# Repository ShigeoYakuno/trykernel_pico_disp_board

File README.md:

# trykernel_pico_disp_board

### 液晶のON/OFF回路
- MOSFETを使います
- 秋月で売っている30円のBSS138 Panjit製を使います
- Vthが1.5Vと使いやすいです
- 300mAしか引けませんが、液晶は100mA程度なので問題ないでしょう
- NチャネルのMOSFETです
- 

### MOSFETの基本回路通りに構成

- 基本回路どおりに設計します
- マイコン側に電流が流れる可能性があるので、直接受けず、抵抗を介します
- オープンドレイン接続を想定し、ゲートはプルダウンしておきます

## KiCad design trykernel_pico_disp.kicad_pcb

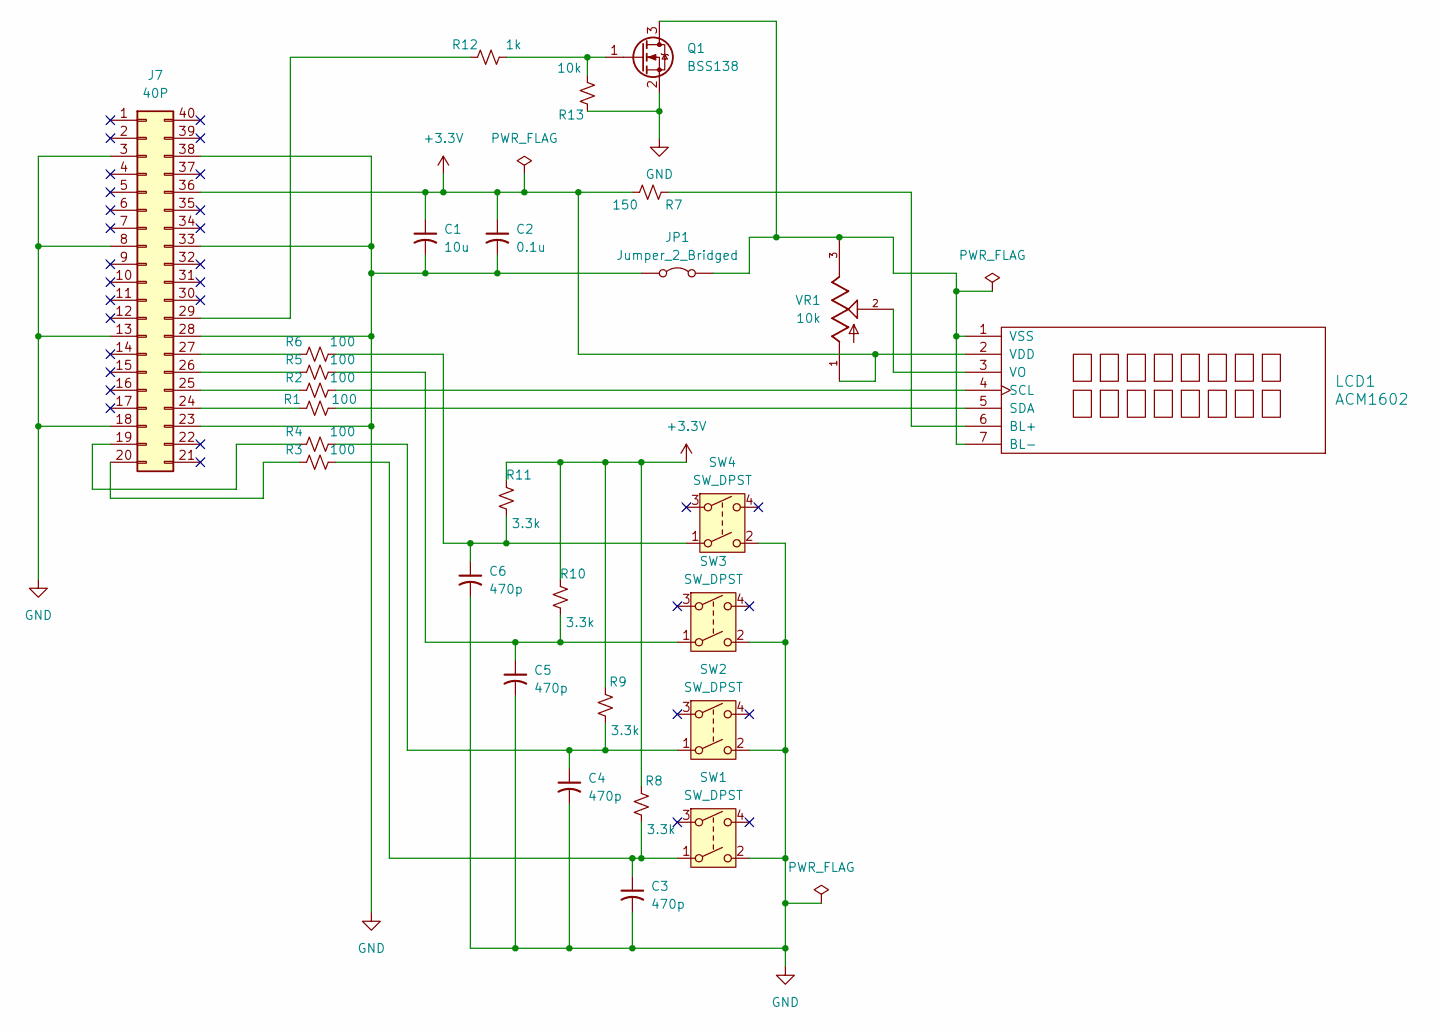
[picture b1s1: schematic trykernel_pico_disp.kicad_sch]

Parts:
C1: 10u; C_0603_1608Metric_Pad1.08x0.95mm_HandSolder
C2: 0.1u; C_0603_1608Metric_Pad1.08x0.95mm_HandSolder
C3, C4, C5, C6: 470p; C_0603_1608Metric_Pad1.08x0.95mm_HandSolder
J7: 40P; RPI_Hat_B+
JP1: Jumper_2_Bridged; PinHeader_1x02_P2.54mm_Vertical
LCD1: ACM1602; I2C_LCD-ACM1602NI-FLW-FBW-M01
Q1: BSS138; SOT-23
R1, R2, R3, R4, R5, R6: 100; R_0603_1608Metric_Pad0.98x0.95mm_HandSolder
R7: 150; R_0603_1608Metric_Pad0.98x0.95mm_HandSolder
R8, R9, R10, R11: 3.3k; R_0603_1608Metric_Pad0.98x0.95mm_HandSolder
R12: 1k; R_0603_1608Metric_Pad0.98x0.95mm_HandSolder
R13: 10k; R_0603_1608Metric_Pad0.98x0.95mm_HandSolder
SW1, SW2, SW3, SW4: SW_DPST; SW_TACT-EVQQ2Y03W
VR1: 10k; TRIM_3362P-1-103; PARTREV 08/26/10

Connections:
+3.3V: C1.1, C2.1, J7.36, LCD1.2 (VDD), R7.2, R8.1, R9.1, R10.1, R11.1, VR1.1
GND: C1.2, C2.2, C3.2, C4.2, C5.2, C6.2, J7.3, J7.8, J7.13, J7.18, J7.23, J7.28, J7.33, J7.38, JP1.1 (A), Q1.2 (S), R13.1, SW1.2, SW2.2, SW3.2, SW4.2
unnamed: C3.1, R3.2, R8.2, SW1.1
unnamed: C4.1, R4.2, R9.2, SW2.1
unnamed: C5.1, R5.2, R10.2, SW3.1
unnamed: C6.1, R6.2, R11.2, SW4.1
unnamed: J7.19, R4.1
unnamed: J7.20, R3.1
unnamed: J7.24, R1.1
unnamed: J7.25, R2.1
unnamed: J7.26, R5.1
unnamed: J7.27, R6.1
unnamed: J7.29, R12.1
unnamed: JP1.2 (B), LCD1.1 (VSS), LCD1.7 (BL-), Q1.3 (D), VR1.3
unnamed: LCD1.6 (BL+), R7.1
unnamed: LCD1.4 (SCL), R2.2
unnamed: LCD1.5 (SDA), R1.2
unnamed: LCD1.3 (VO), VR1.2
unnamed: Q1.1 (G), R12.2, R13.2

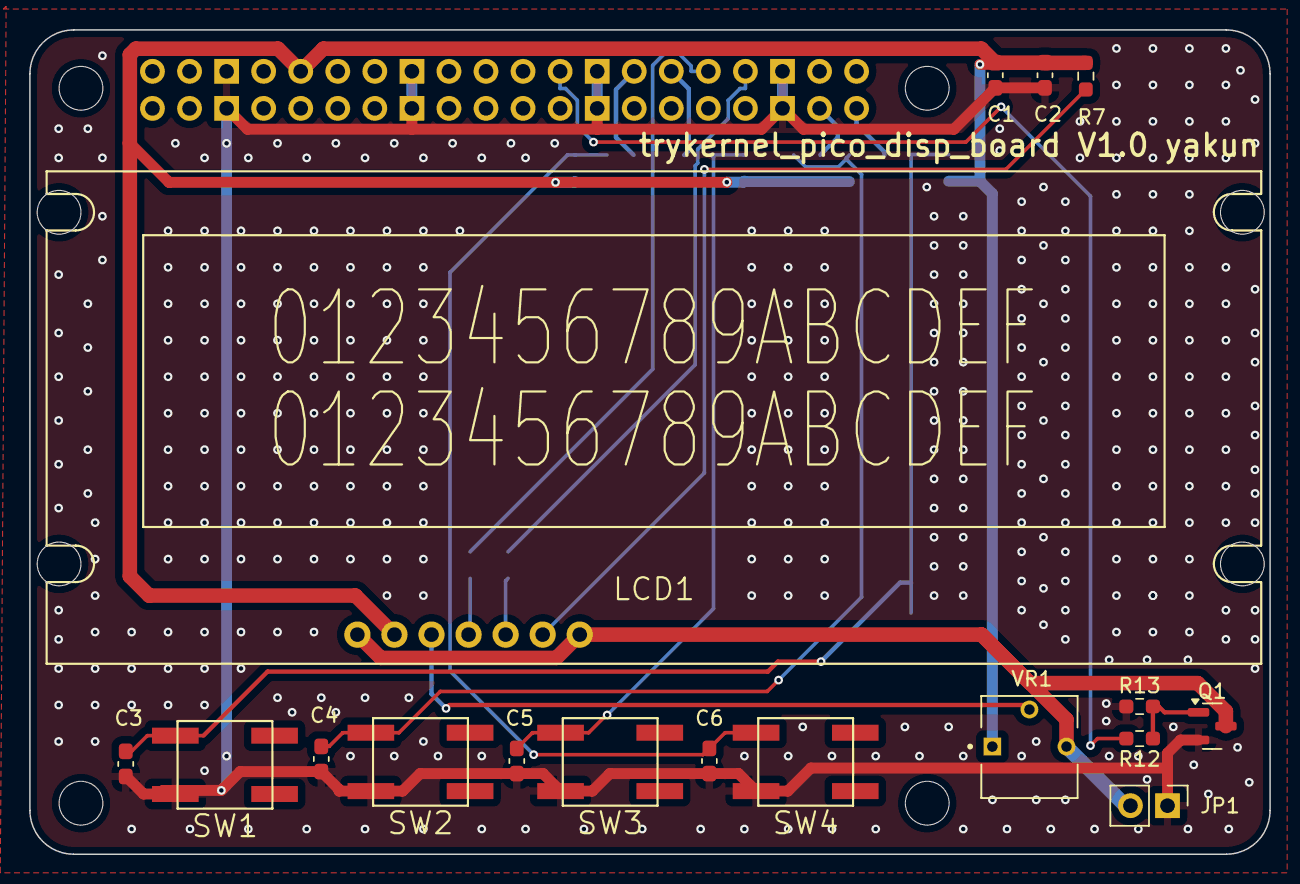
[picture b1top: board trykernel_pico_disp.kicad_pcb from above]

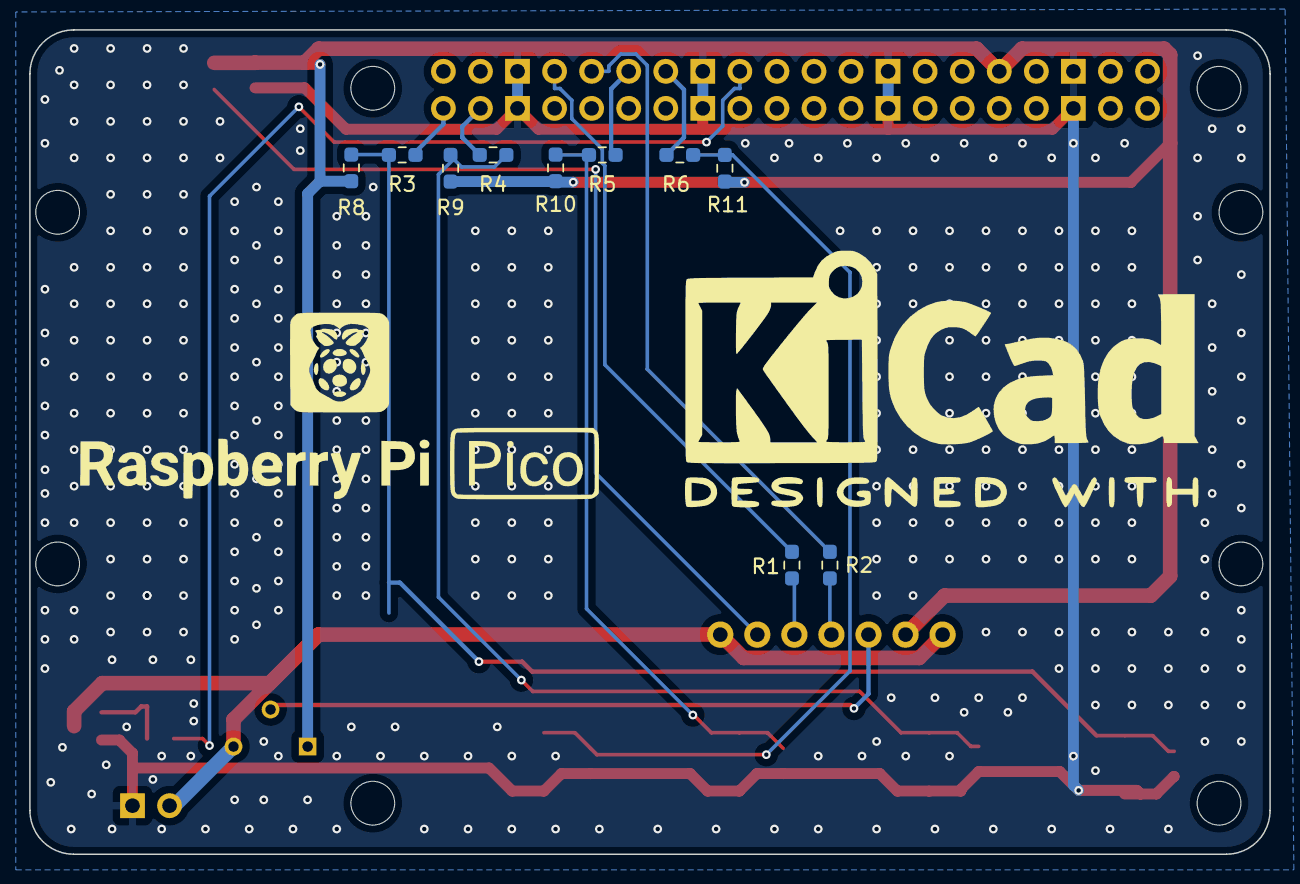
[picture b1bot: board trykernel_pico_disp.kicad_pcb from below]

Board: 2 copper layers, 85.0 x 56.5 mm, 28 parts (10 on the bottom side), 19 nets.

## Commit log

2025-05-14 version 1.0 発注
